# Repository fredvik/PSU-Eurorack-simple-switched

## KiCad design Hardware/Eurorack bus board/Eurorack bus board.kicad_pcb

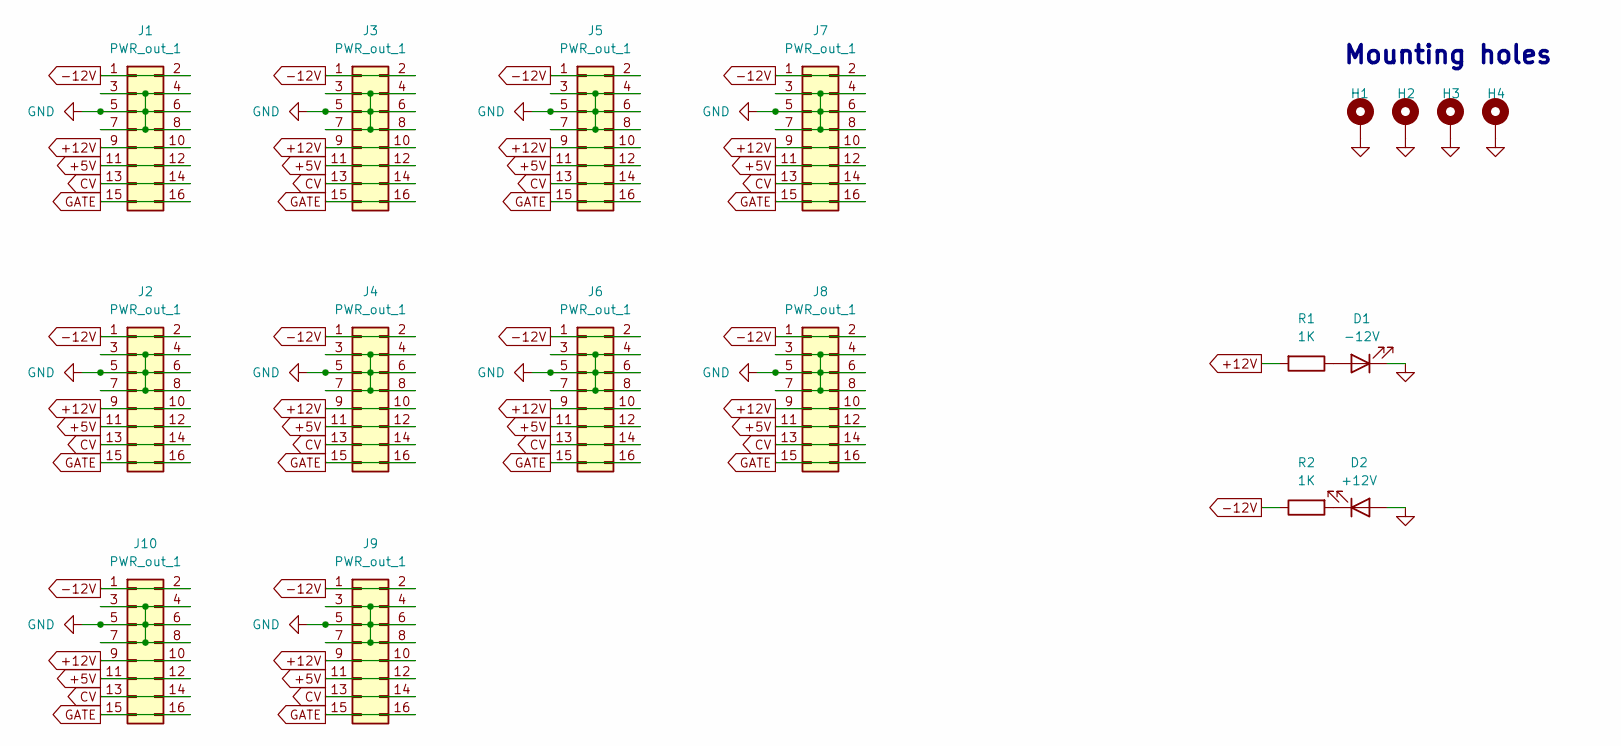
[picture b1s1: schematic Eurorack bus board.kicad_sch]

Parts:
D1: -12V; LED_D3.0mm
D2: +12V; LED_D3.0mm
H1, H2, H3, H4: MountingHole; MountingHole_3.2mm_M3_Pad
J1, J2, J3, J4, J5, J6, J7, J8, J9, J10: PWR_out_1; IDC-Header_2x08_vert_Eurorack_PWR_combo
R1, R2: 1K; R_Axial_DIN0207_L6.3mm_D2.5mm_P7.62mm_Horizontal

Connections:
+5V: J1.11, J1.12, J2.11, J2.12, J3.11, J3.12, J4.11, J4.12, J5.11, J5.12, J6.11, J6.12, J7.11, J7.12, J8.11, J8.12, J9.11, J9.12, J10.11, J10.12
+12V: J1.9, J1.10, J2.9, J2.10, J3.9, J3.10, J4.9, J4.10, J5.9, J5.10, J6.9, J6.10, J7.9, J7.10, J8.9, J8.10, J9.9, J9.10, J10.9, J10.10, R1.2
-12V: J1.1, J1.2, J2.1, J2.2, J3.1, J3.2, J4.1, J4.2, J5.1, J5.2, J6.1, J6.2, J7.1, J7.2, J8.1, J8.2, J9.1, J9.2, J10.1, J10.2, R2.1
CV: J1.13, J1.14, J2.13, J2.14, J3.13, J3.14, J4.13, J4.14, J5.13, J5.14, J6.13, J6.14, J7.13, J7.14, J8.13, J8.14, J9.13, J9.14, J10.13, J10.14
GATE: J1.15, J1.16, J2.15, J2.16, J3.15, J3.16, J4.15, J4.16, J5.15, J5.16, J6.15, J6.16, J7.15, J7.16, J8.15, J8.16, J9.15, J9.16, J10.15, J10.16
GND: D1.1 (K), D2.2 (A), H1.1, H2.1, H3.1, H4.1, J1.3, J1.4, J1.5, J1.6, J1.7, J1.8, J2.3, J2.4, J2.5, J2.6, J2.7, J2.8, J3.3, J3.4, J3.5, J3.6, J3.7, J3.8, J4.3, J4.4, J4.5, J4.6, J4.7, J4.8, J5.3, J5.4, J5.5, J5.6, J5.7, J5.8, J6.3, J6.4, J6.5, J6.6, J6.7, J6.8, J7.3, J7.4, J7.5, J7.6, J7.7, J7.8, J8.3, J8.4, J8.5, J8.6, J8.7, J8.8, J9.3, J9.4, J9.5, J9.6, J9.7, J9.8, J10.3, J10.4, J10.5, J10.6, J10.7, J10.8
unnamed: D1.2 (A), R1.1
unnamed: D2.1 (K), R2.2

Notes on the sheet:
Mounting holes

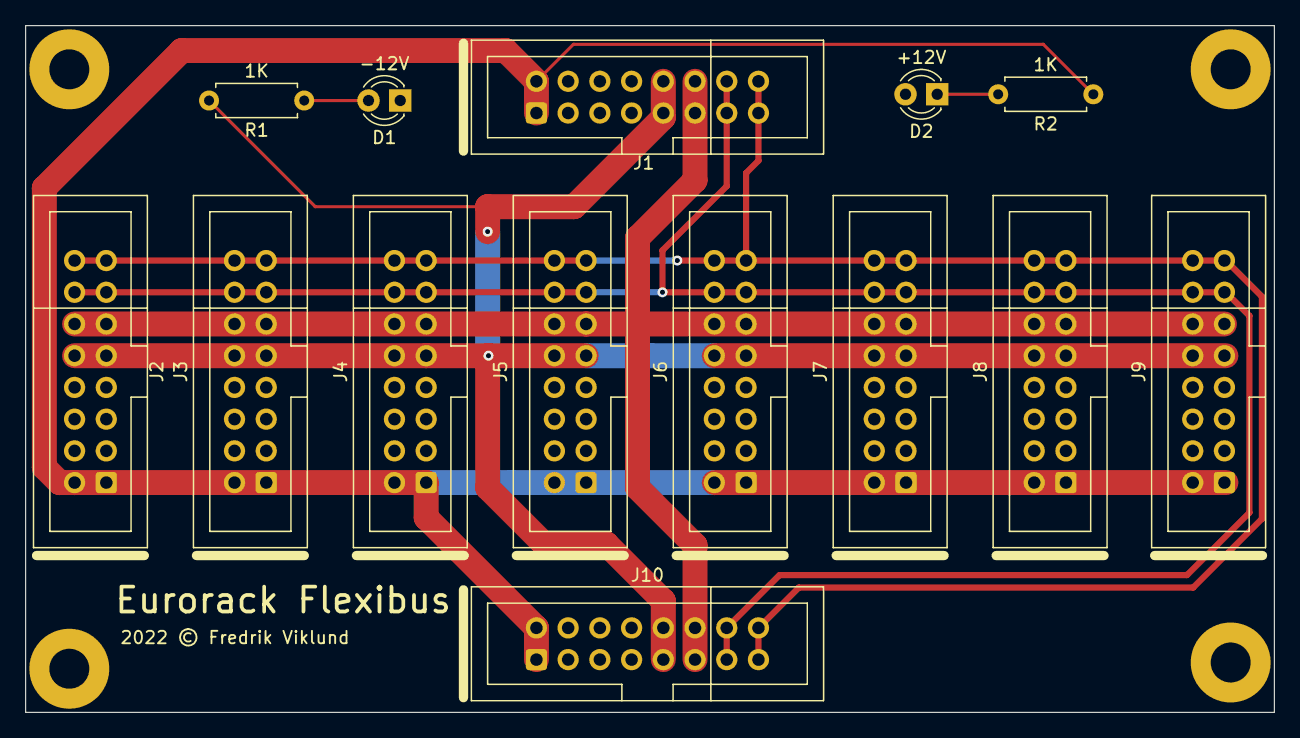
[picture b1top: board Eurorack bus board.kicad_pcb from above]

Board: 2 copper layers, 100.0 x 55.0 mm, 18 parts (0 on the bottom side), 8 nets.

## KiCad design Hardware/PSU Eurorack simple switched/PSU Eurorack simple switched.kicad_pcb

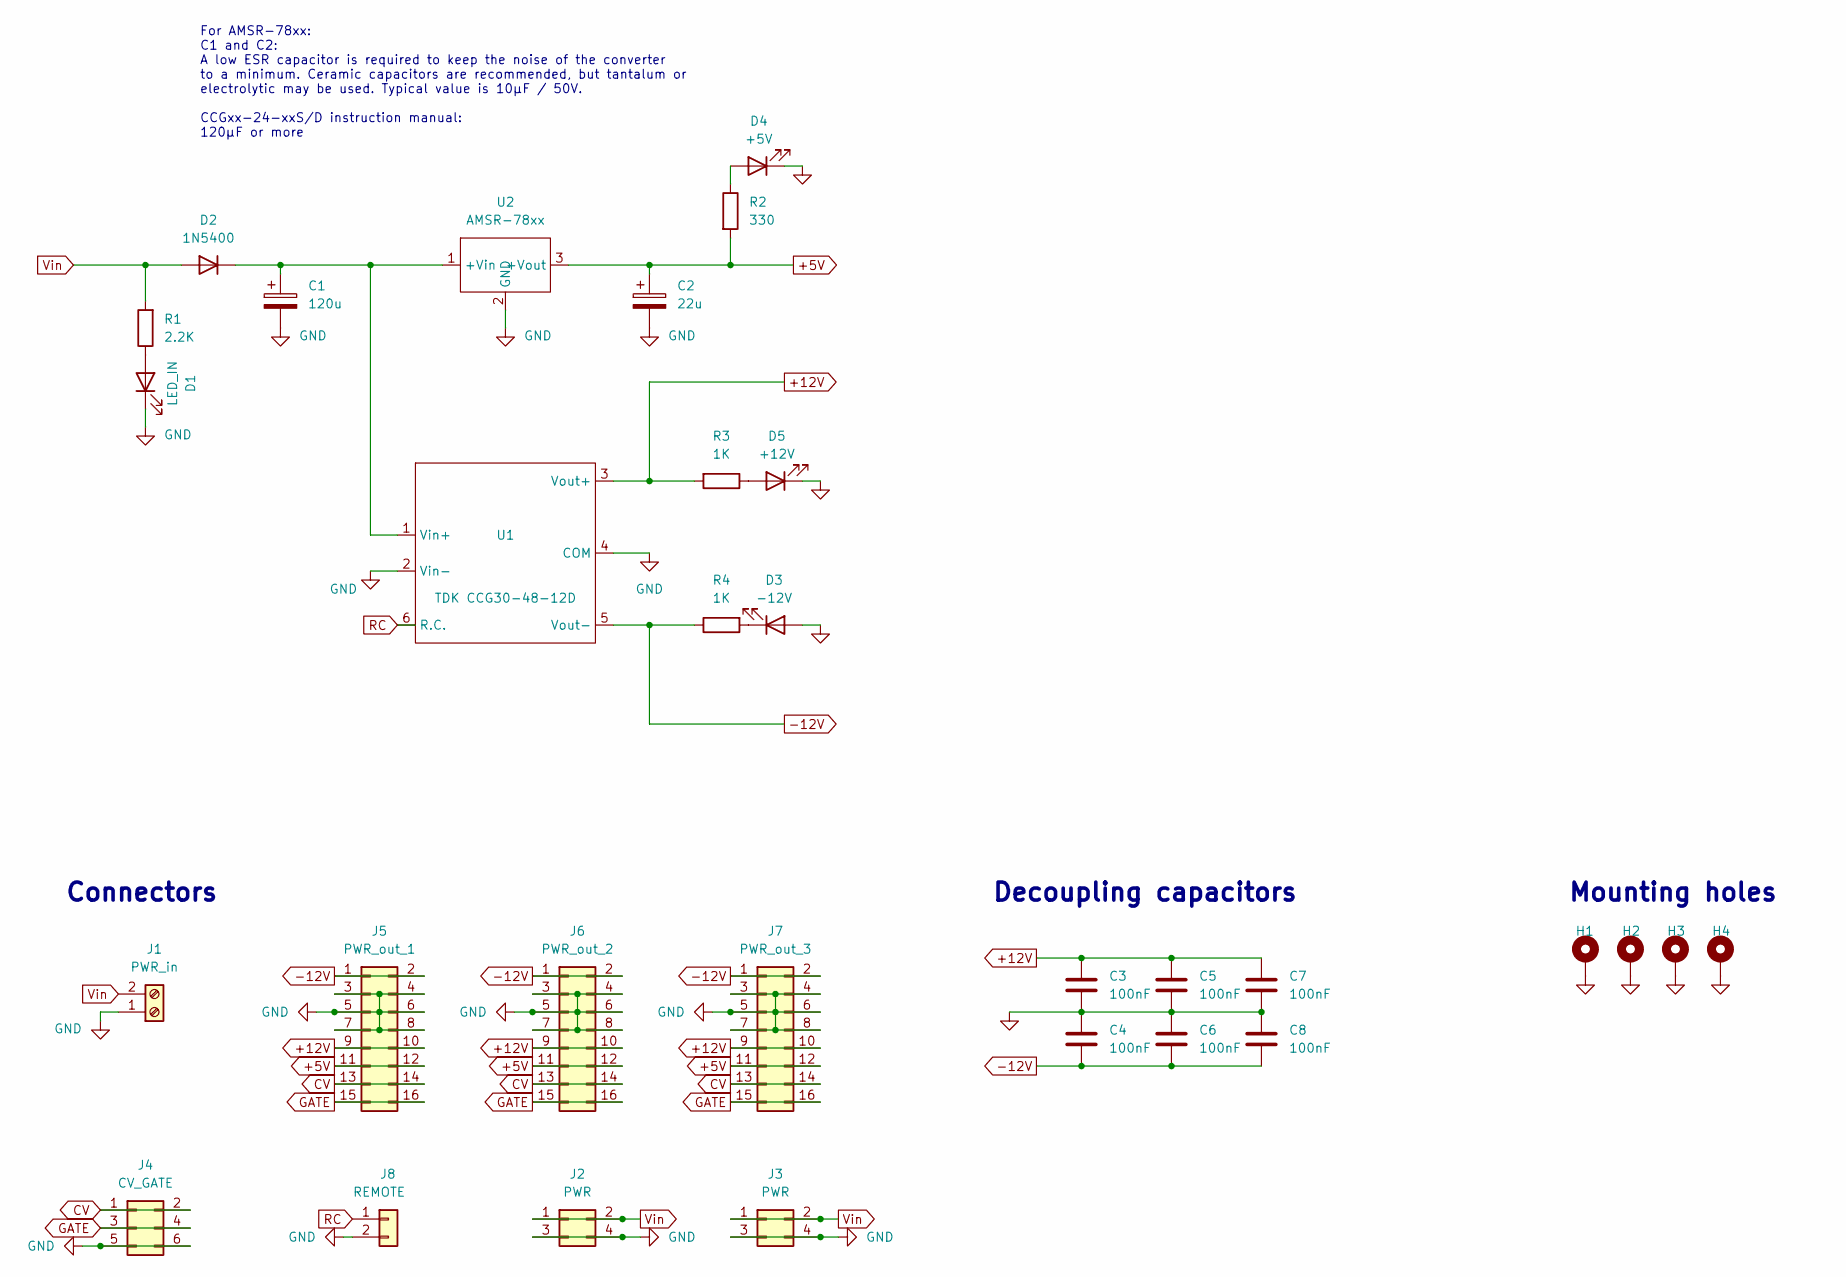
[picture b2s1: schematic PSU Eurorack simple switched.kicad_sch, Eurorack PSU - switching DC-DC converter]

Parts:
C1: 120u; CP_Radial_D10.0mm_P3.50mm
C2: 22u; CP_Radial_D5.0mm_P2.00mm
C3, C4, C5, C6, C7, C8: 100nF; C_Disc_D7.0mm_W2.5mm_P5.00mm
D1: LED_IN; LED_D3.0mm
D2: 1N5400; D_DO-201AD_P15.24mm_Horizontal
D3: -12V; LED_D3.0mm
D4: +5V; LED_D3.0mm
D5: +12V; LED_D3.0mm
H1, H2, H3, H4: MountingHole; MountingHole_3.2mm_M3_Pad
J1: PWR_in; TerminalBlock_bornier-2_P5.08mm
J2, J3: PWR; Molex_Mini-Fit_Jr_5569-04A2_2x02_P4.20mm_Horizontal - Vin_G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
J4: CV_GATE; PinHeader_2x03_P2.54mm_Vertical
J5: PWR_out_1; IDC-Header_2x08_vert_Eurorack_PWR_combo
J6: PWR_out_2; IDC-Header_2x08_vert_Eurorack_PWR_combo
J7: PWR_out_3; IDC-Header_2x08_vert_Eurorack_PWR_combo
J8: REMOTE; PinHeader_2x01_P2.54mm_Vertical
R1: 2.2K; R_Axial_DIN0207_L6.3mm_D2.5mm_P7.62mm_Horizontal
R2: 330; R_Axial_DIN0207_L6.3mm_D2.5mm_P7.62mm_Horizontal
R3, R4: 1K; R_Axial_DIN0207_L6.3mm_D2.5mm_P7.62mm_Horizontal
U1: TDK CCG30-48-12D; DKMW30
U2: AMSR-78xx; R-785.0-0.5

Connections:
+5V: C2.1, J5.11, J5.12, J6.11, J6.12, J7.11, J7.12, R2.2, U2.3 (+Vout)
+12V: C3.1, C5.1, C7.1, J5.9, J5.10, J6.9, J6.10, J7.9, J7.10, R3.2, U1.3 (Vout+)
-12V: C4.2, C6.2, C8.2, J5.1, J5.2, J6.1, J6.2, J7.1, J7.2, R4.1, U1.5 (Vout-)
CV: J4.1, J4.2, J5.13, J5.14, J6.13, J6.14, J7.13, J7.14
GATE: J4.3, J4.4, J5.15, J5.16, J6.15, J6.16, J7.15, J7.16
GND: C1.2, C2.2, C3.2, C4.1, C5.2, C6.1, C7.2, C8.1, D1.1 (K), D3.2 (A), D4.1 (K), D5.1 (K), H1.1, H2.1, H3.1, H4.1, J1.1, J2.3, J2.4, J3.3, J3.4, J4.5, J4.6, J5.3, J5.4, J5.5, J5.6, J5.7, J5.8, J6.3, J6.4, J6.5, J6.6, J6.7, J6.8, J7.3, J7.4, J7.5, J7.6, J7.7, J7.8, J8.2, U1.2 (Vin-), U1.4 (COM), U2.2 (GND)
unnamed: C1.1, D2.1 (K), U1.1 (Vin+), U2.1 (+Vin)
unnamed: D1.2 (A), R1.1
unnamed: D3.1 (K), R4.2
unnamed: D4.2 (A), R2.1
unnamed: D5.2 (A), R3.1
RC: J8.1, U1.6 (R.C.)
Vin: D2.2 (A), J1.2, J2.1, J2.2, J3.1, J3.2, R1.2

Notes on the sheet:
Decoupling capacitors
For AMSR-78xx: C1 and C2: A low ESR capacitor is required to keep the noise of the converter to a minimum. Ceramic capacitors are recommended, but tantalum or electrolytic may be used. Typical value is 10μF / 50V. CCGxx-24-xxS/D instruction manual: 120μF or more
Connectors
Mounting holes

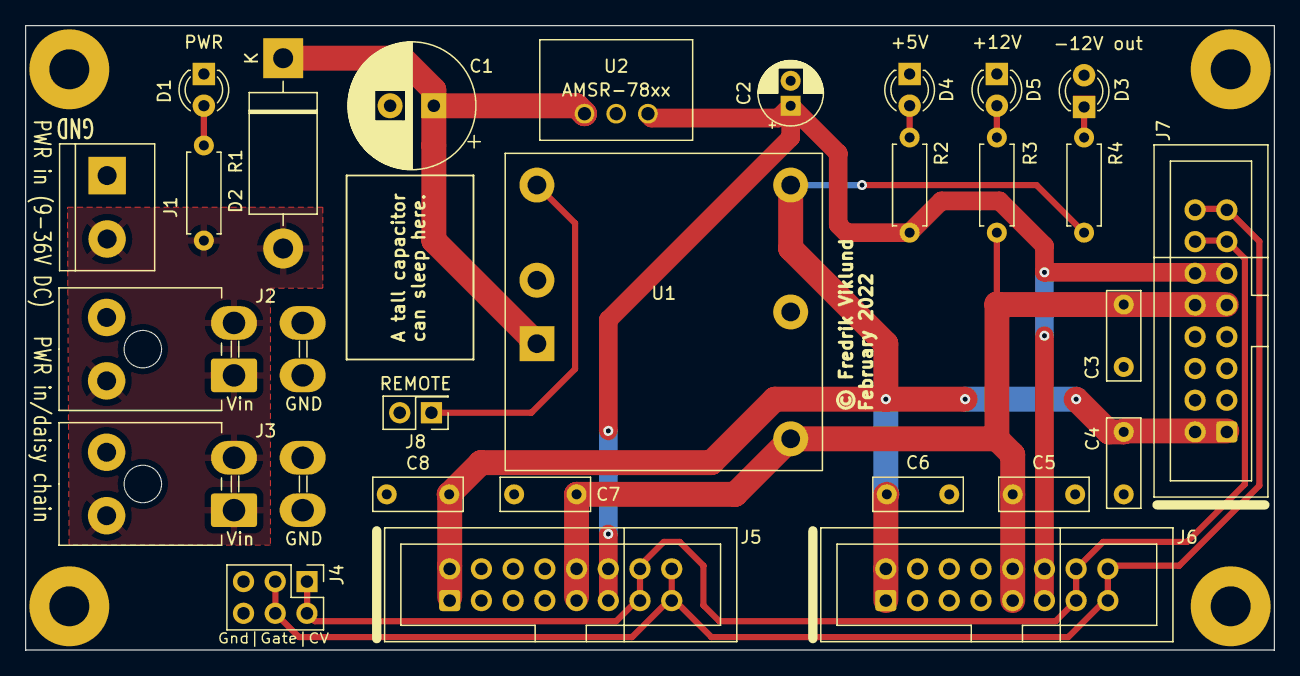
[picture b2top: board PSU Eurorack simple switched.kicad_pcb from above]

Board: 2 copper layers, 100.0 x 50.0 mm, 31 parts (0 on the bottom side), 13 nets.

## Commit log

2022-01-15 First version, as ordered from Aisler
2022-01-15 Add folder structure
2022-02-08 Swapped polarity of -12V LED, added remote control header, enlarged input area, fixed text placements
2022-05-27 Bus board first version with gerbers

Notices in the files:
Hardware/Eurorack bus board/Eurorack bus board.kicad_pcb:
2022 © Fredrik Viklund
